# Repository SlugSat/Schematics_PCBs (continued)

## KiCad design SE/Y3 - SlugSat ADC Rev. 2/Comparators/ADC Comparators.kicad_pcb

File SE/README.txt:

Rad Team Six shall live forever in our Memories

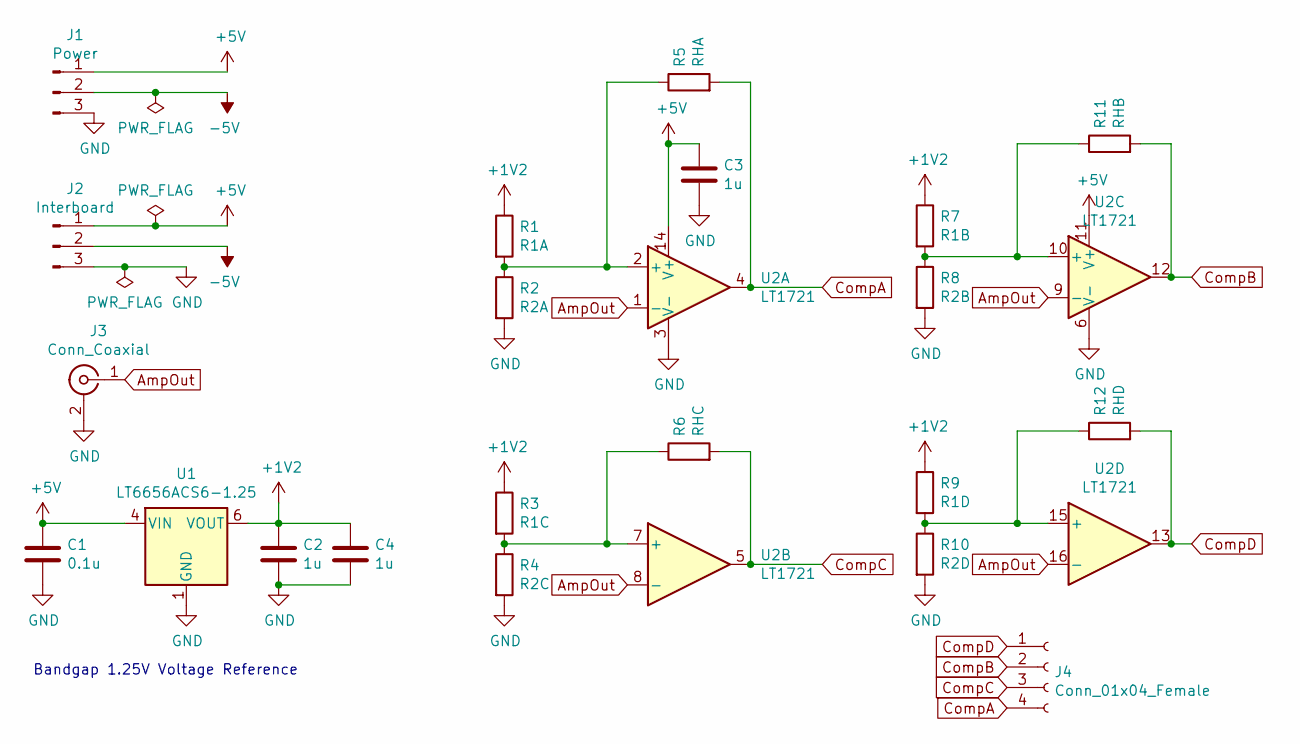
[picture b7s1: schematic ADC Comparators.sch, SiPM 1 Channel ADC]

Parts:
C1: 0.1u; C_0805_2012Metric_Pad1.15x1.40mm_HandSolder
C2, C3, C4: 1u; C_0805_2012Metric_Pad1.15x1.40mm_HandSolder
J1: Power; PinSocket_1x03_P2.54mm_Vertical
J2: Interboard; PinSocket_1x03_P2.54mm_Vertical
J3: Conn_Coaxial; SMA_Amphenol_132289_EdgeMount
J4: Conn_01x04_Female; PinSocket_1x04_P2.54mm_Vertical
R1: R1A; R_0805_2012Metric_Pad1.15x1.40mm_HandSolder
R2: R2A; R_0805_2012Metric_Pad1.15x1.40mm_HandSolder
R3: R1C; R_0805_2012Metric_Pad1.15x1.40mm_HandSolder
R4: R2C; R_0805_2012Metric_Pad1.15x1.40mm_HandSolder
R5: RHA; R_0805_2012Metric_Pad1.15x1.40mm_HandSolder
R6: RHC; R_0805_2012Metric_Pad1.15x1.40mm_HandSolder
R7: R1B; R_0805_2012Metric_Pad1.15x1.40mm_HandSolder
R8: R2B; R_0805_2012Metric_Pad1.15x1.40mm_HandSolder
R9: R1D; R_0805_2012Metric_Pad1.15x1.40mm_HandSolder
R10: R2D; R_0805_2012Metric_Pad1.15x1.40mm_HandSolder
R11: RHB; R_0805_2012Metric_Pad1.15x1.40mm_HandSolder
R12: RHD; R_0805_2012Metric_Pad1.15x1.40mm_HandSolder
U1: LT6656ACS6-1.25; TSOT-23-6_HandSoldering
U2: LT1721; SOIC-16_3.9x9.9mm_P1.27mm

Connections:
+1V2: C2.1, C4.1, R1.1, R3.1, R7.1, R9.1, U1.6 (VOUT)
+5V: C1.1, C3.1, J1.1, J2.1, U1.4 (VIN), U2.11 (V+), U2.14 (V+)
-5V: J1.2, J2.2
AmpOut: J3.1 (In), U2.1 (-), U2.8 (-), U2.9 (-), U2.16 (-)
CompA: J4.4, R5.2, U2.4
CompB: J4.2, R11.2, U2.12
CompC: J4.3, R6.2, U2.5
CompD: J4.1, R12.2, U2.13
GND: C1.2, C2.2, C3.2, C4.2, J1.3, J2.3, J3.2 (Ext), R2.2, R4.2, R8.2, R10.2, U1.1 (GND), U1.2 (GND), U2.3 (V-), U2.6 (V-)
unnamed: R1.2, R2.1, R5.1, U2.2 (+)
unnamed: R3.2, R4.1, R6.1, U2.7 (+)
unnamed: R9.2, R10.1, R12.1, U2.15 (+)
unnamed: R7.2, R8.1, R11.1, U2.10 (+)

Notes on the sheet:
Bandgap 1.25V Voltage Reference

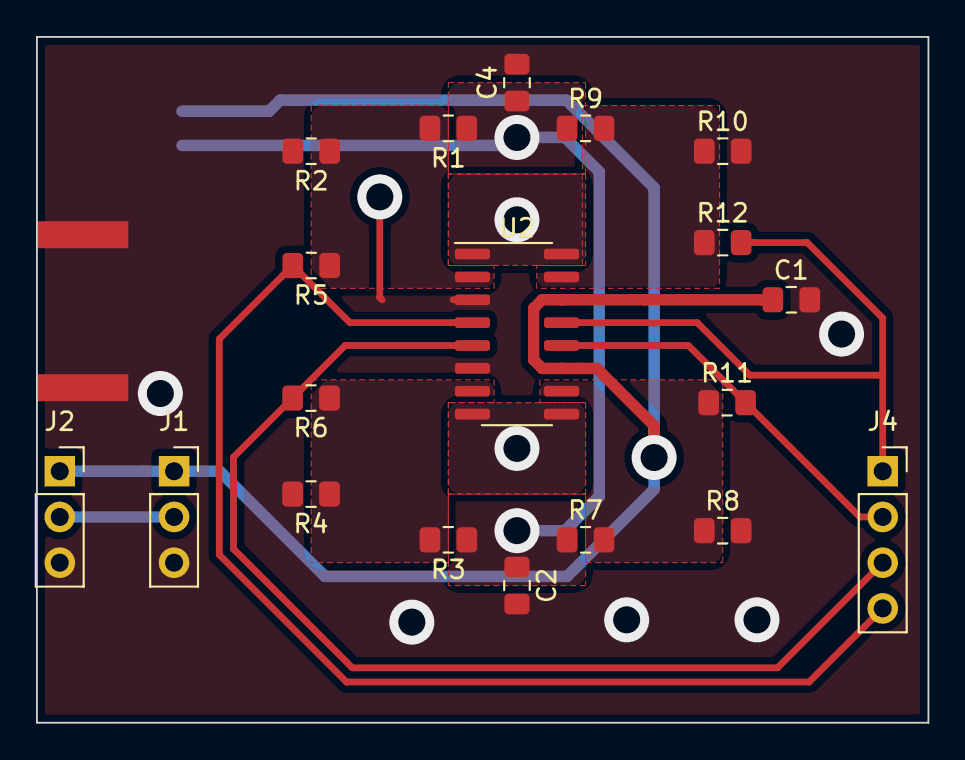
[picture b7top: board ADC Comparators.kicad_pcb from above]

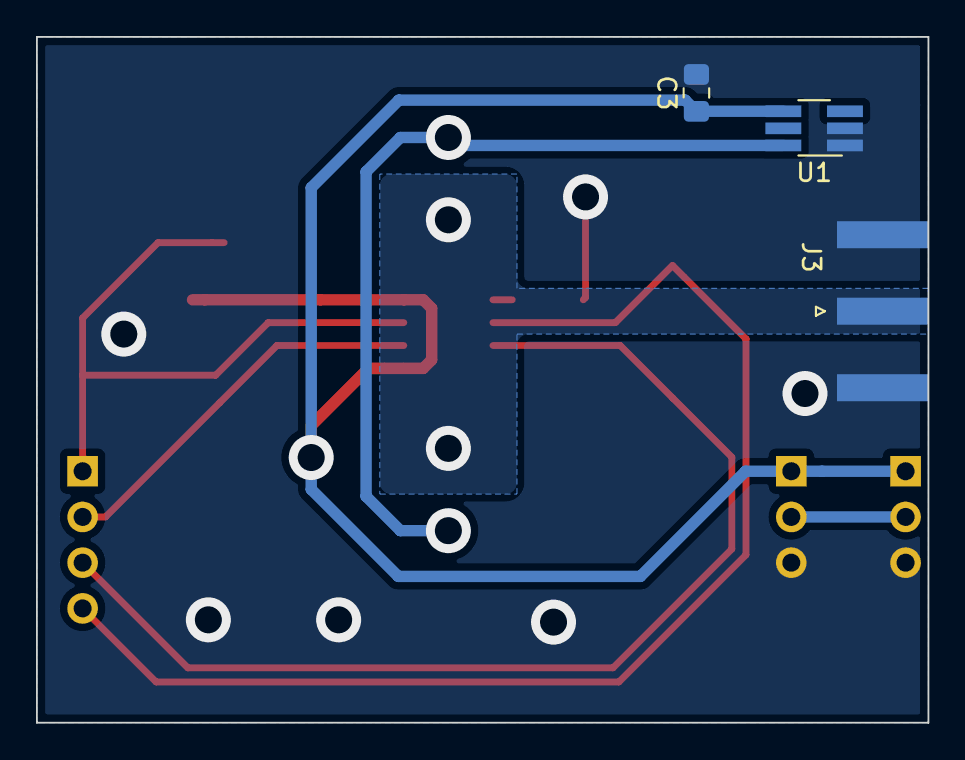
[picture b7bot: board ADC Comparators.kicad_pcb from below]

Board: 2 copper layers, 49.5 x 38.1 mm, 22 parts (3 on the bottom side), 13 nets.

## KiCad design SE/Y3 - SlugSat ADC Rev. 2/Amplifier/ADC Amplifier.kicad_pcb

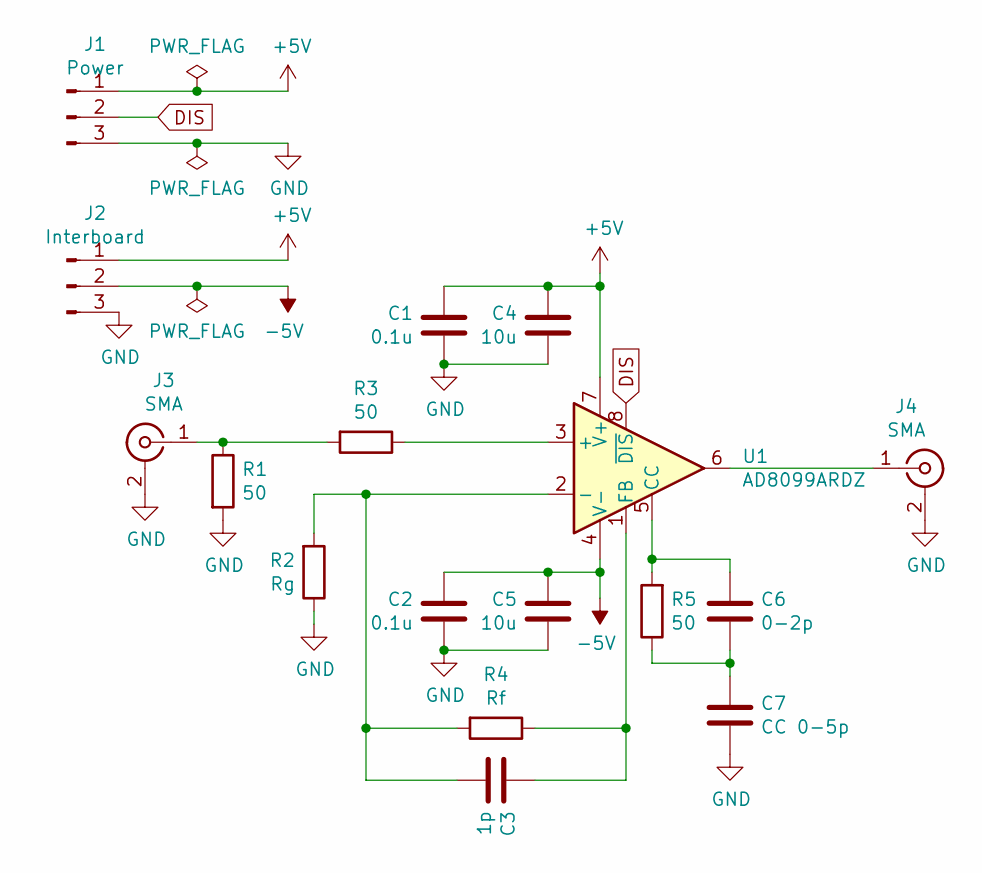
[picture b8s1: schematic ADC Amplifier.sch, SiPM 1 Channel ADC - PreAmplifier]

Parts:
C1, C2: 0.1u; C_0805_2012Metric_Pad1.15x1.40mm_HandSolder
C3: 1p; C_0805_2012Metric_Pad1.15x1.40mm_HandSolder
C4, C5: 10u; C_Elec_4x5.4
C6: 0-2p; C_0805_2012Metric_Pad1.15x1.40mm_HandSolder
C7: CC 0-5p; C_0805_2012Metric_Pad1.15x1.40mm_HandSolder
J1: Power; PinSocket_1x03_P2.54mm_Vertical
J2: Interboard; PinSocket_1x03_P2.54mm_Vertical
J3, J4: SMA; SMA_Amphenol_132289_EdgeMount
R1, R3, R5: 50; R_0805_2012Metric_Pad1.15x1.40mm_HandSolder
R2: Rg; R_0805_2012Metric_Pad1.15x1.40mm_HandSolder
R4: Rf; R_0805_2012Metric_Pad1.15x1.40mm_HandSolder
U1: AD8099ARDZ; SOIC-8_3.9x4.9mm_P1.27mm

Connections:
+5V: C1.1, C4.1, J1.1, J2.1, U1.7 (V+)
-5V: C2.1, C5.1, J2.2, U1.4 (V-)
DIS: J1.2, U1.8 (~DIS)
GND: C1.2, C2.2, C4.2, C5.2, C7.2, J1.3, J2.3, J3.2 (Ext), J4.2 (Ext), R1.2, R2.1, U1.9 (GND)
unnamed: C3.1, R4.1, U1.1 (FB)
unnamed: C3.2, R2.2, R4.2, U1.2 (-)
unnamed: C6.1, R5.2, U1.5 (CC)
unnamed: C6.2, C7.1, R5.1
unnamed: J3.1 (In), R1.1, R3.2
unnamed: J4.1 (In), U1.6
unnamed: R3.1, U1.3 (+)

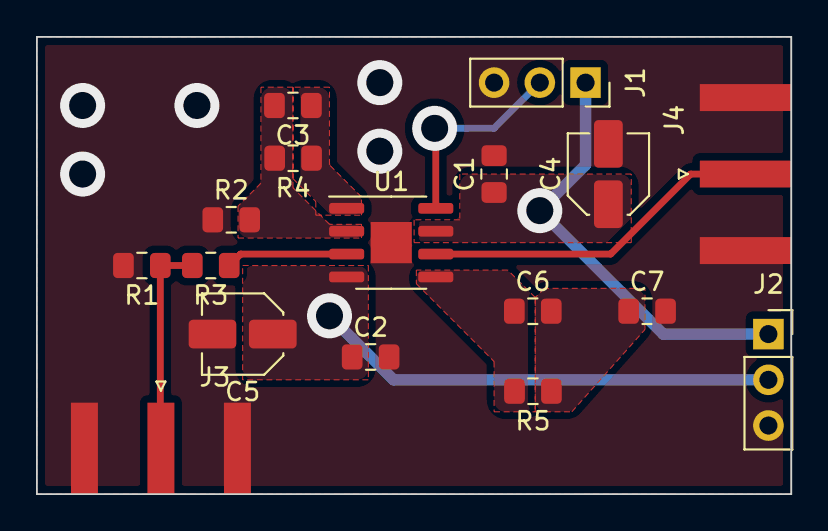
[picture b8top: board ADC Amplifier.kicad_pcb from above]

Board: 2 copper layers, 41.9 x 25.4 mm, 17 parts (0 on the bottom side), 11 nets.

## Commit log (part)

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2020-01-04 created folder for footprints and schematics. created folders for all sub teams. Populated LT schematics and PCB files
2020-01-04 needed ssh key
2020-01-10 Update test-file.txt
    dummy text
2020-01-15 added edge cuts
2020-01-16 added README files for the rest of the subteams
2020-01-16 added read me to all subteam folders
2020-01-16 created 29.4MHz LPF Schematic
2020-01-16 Created Variable Capacitor footprint. Completed rev0 of 29.4MHz low-pass filter.
2020-01-17 removed 0 ohm resistors on 29.4MHz LPF
2020-01-18 removed 0 ohm resistors
2020-01-19 added PLL PSPICE simulations
2020-01-19 29.4 MHz Bandpass Added
    I put all of my documents regarding the 29.4 MHz Bandpass Filter onto Git
2020-01-22 created notch filter schematic
2020-01-22 created schematic symbol and footprint for 7m3 inductor. laid out PCB
2020-01-25 changing EMS file name to EPS
2020-01-29 created README
2020-01-29 PLL and bandstop PSPICE changes
2020-01-29 removed README due to merge conflict?? i just added it back in. no other changes were made. sorry EPS
2020-01-30 creating basic schematic of SPV1040 charger
2020-02-01 changed power amplifier pcb layout again
2020-02-02 added RF transformer datasheets in the PA folder
2020-02-02 adding spreadsheet that includes calculations for SPV1040
2020-02-03 Added SS.lib to schematic libraries, Added SS.pretty to footprints, added .stp to /Chassis
2020-02-04 adding README for calculations folder within SPV1040 and moving paramters of python code to top
2020-02-04 adding resistor values found from 308 inventory spreadsheet
2020-02-04 updating github
2020-02-04 Changes to 29.4 MHz Bandpass Filter
    I made some changes to my best filter design, allowing for series inductors
2020-02-04 added step file to A1 and B1
2020-02-04 fixed step file for A1 and B1
2020-02-05 Kicad Valentine's File
    Just in case you want to edit the text for the heart, but keep the heart itself, I uploaded the kicad PCB file
2020-02-05 made mechanical drawings for STD PCB's
2020-02-06 fixed Step files for A1/A2/B1/B2
2020-02-06 no changes to bandpass filter
2020-02-07 Variable Inductors, 5th Order Chev, Kicad Tutorial
    - I made a Filter with variable inductors
    - I made a 5th order Chebyshev Filter
    - I made a folder to put Kicad tutorial testing files in
2020-02-08 added PA rev 2.0 schematic
2020-02-08 adding datasheet for potential capacitor
2020-02-08 Finished PA Rev 2.0 layout and ready to mill
2020-02-10 Clock Test board v1.0
2020-02-11 Saved schematic and PCB
2020-02-11 add footprint to library
2020-02-12 created down mixer schematic in kicad
2020-02-13 created mixer schematic and rev2 with impedance matching w/o transormers (single-ended)
2020-02-14 Added 50 Ohm microstrip to SS.lib and SS.pretty
2020-02-14 fixed Clock Test
2020-02-15 LNA uploaded to Kicad
    I recreated Year 2's LNA board on Kicad and made a quick PCB
2020-02-15 Bandpass Filter Cleaning
    I reorganized the 29.4 MHz bandpass filter designs so it's more readable in the folders, and shows which file is the final design
2020-02-15 created layout for single-ended down mixer
2020-02-16 swapped edge mount footprint. created gerber and drill files.
2020-02-17 completing the values for capacitors in SPV1040 and choosing the diode for over output voltage...Adding 0 ohm resistor for XSHUT descision later
2020-02-17 PA rev 3.0 schematic and footprint association complete
2020-02-18 updated footprint assignments to daughter board
2020-02-18 revised PA rev 3.0 schematic and started PCB layout
2020-02-18 Fixed PA rev 2.0 schematic values for PA rev 2.1
2020-02-18 Finished Mother Board
    Each of the Components have been placed to the mother board
2020-02-18 Daughter Board
    Began annotating the rest of the Daughter board
2020-02-19 Finished Daughter Board
    I finished assigning the footprints to the daughter board
2020-02-19 Just a push check
    idk if I pushed
2020-02-19 Messing With Resistors
    Just doing some resistor changes but idk if it worked
2020-02-19 LMX2313 3D view
    Added an imposted 3D viewer for the LMX2313
2020-02-19 Added LMX2313 3D again
2020-02-19 finished Mobo footprint/3D placement
2020-02-19 making multiple changes to board. Changing capacitor at input and output to 100uF and adding footprints to pcb
2020-02-19 adding TSSOP8 footprint into SS footprint library for SPV1040. Also referenced footprint to the one in SS within the PCB layout
2020-02-19 finshed assigning step files for integration boards
2020-02-19 removed step files from repo because they were large files
2020-02-19 changing input values into float to take decimals
2020-02-19 creating schematic for Lithion charger l6924 and adding schematic symbol into library ss
2020-02-20 Finished Variable Gain Amplifier
    I finished moving the Variable Gain Amplifier onto Kicad, following the board layout made by Sage
2020-02-21 remaking schematic from Pierce back to Colpitts
2020-02-21 MoBo Pretty
    Made some changes to the MoBo which included changing the outline boarders for the sheets
2020-02-21 working on voting circuit
2020-02-22 completing charging circuit L6924D
2020-02-23 adding the SS schematic and footprint library
2020-02-23 adding L6924D footprint into SS footprint library
2020-02-23 shrinking pcb layout
2020-02-23 PLL Stability Test Rev0 Schematic
    I made a new folder for the PLL stability test. I began placing generic 8 pin op-amps between the loop filter and the VCO
2020-02-23 Cleaned Up Stability Test Board
    Made the schematic page bigger
2020-02-23 Bwtest rev2
    Uploaded burn wire rev2 .drl files
2020-02-23 -5V
    Added -5V rail
2020-02-23 -5V rail updates
    -5V rail schematic
2020-02-23 saving
2020-02-25 Pre-Amp File
    I fully integrated the Pre-amp onto KiCad
2020-02-25 Stability Test PCB design
    I laid out the PCB for the stability test
2020-02-25 Added label for Stability Board
2020-02-26 adding ignore file
2020-02-26 gitignore for kicad files
2020-02-27 completed down-mixer rev0.1 schematic and layout. generated milling files
2020-02-27 Added 40.1 MHz LPF on KiCad
    I added the 40.1 MHz Low Pass Filter onto KiCad
2020-02-28 New footprint
    Added SL03 Vishay footprint
2020-02-28 added footprint into SS.pretty for EPS
2020-02-29 Imported Rev4.01, 4.02, 4.03 to Kicad
    Put Rev4.01, Rev4.02, and Rev4.03 onto KiCad
2020-02-29 Revised PA Rev 3.0 layout to fix transformers from coupling
2020-02-29 Finished PLL Revisions on KiCad
    The KiCad files for the PLL have been uploaded to github and the integration to the "Real Resistor" symbol has begun
2020-03-01 Nothing Really
2020-03-01 Changed Resistor Symbols
    Fixed the resistor symbols from PLL Rev 4.1-4.3
2020-03-02 Just Testing GitBash, changed a resistor value in LNA
2020-03-02 removed .net from .gitignore
2020-03-02 Added a symbol to one of the notch filters
2020-03-02 add dummy component
2020-03-02 Important changes to notch filter
2020-03-03 -5V rail
    -5V rail updated layout
2020-03-04 files
    files
2020-03-04 Made a separate op-amp board
2020-03-05 completed PLL stability test layour for individual boards
2020-03-05 Nothing much I don't think
2020-03-06 Finished the layout for the Op-Amp Test Board with Capacitors
2020-03-06 .DS_store files
    File changes
2020-03-06 -5V Rail
    Updated PCB layout
2020-03-06 -5V Rail
    Update 2 PCB layout
2020-03-06 added PA coupler datasheet
2020-03-07 changing scalar and bias due to improvement in dummy circuit
2020-03-07 manipulated bais to get better values
2020-03-07 PA Rev 4.0 layout is complete. PCB is ready to be milled
2020-03-08 Added the schematic for SE's flash memory board
2020-03-09 Added PA Rev 4.1 KiCAD schematic files
2020-03-09 PA Rev 4.1 KiCAD schematic complete.
2020-03-09 PA Rev 4.1 KiCAD schematic and footprint association is complete. Ready for PCB layout
2020-03-09 PA Rev 4.1 PCB layout still in progress.
2020-03-10 Finished SE Flash Memory Schematic
2020-03-10 finishing 1.5 version of spv1040
2020-03-10 3.3V Rail
    Schematic
2020-03-10 Changed an input pin to the flash memory for SE schematic
2020-03-11 created matlab files for VCO. updated phase detector board for stability test
2020-03-11 Update 3.3V_Rail.sch
    Update v.0.1
2020-03-12 added second matlab vco sim
2020-03-12 -5V rail
    Schematic update
2020-03-17 03/16/2020 10:07 PM. last commit from UCSC campus. good bye.
2020-04-01 Trying stuff
2020-04-06 I uploaded the schematics for the receiving stage into their respective hierarchial sheets and have begun the integration of the received stage
2020-04-08 Added simple amplifier simulation to get used to simulink
2020-04-08 simple amplifier model (SAM) simulink simulation works!
2020-04-10 Included a graph of for my self made VCO which shows the frequency change with a change in 0-5V, with steps of 0.2V
2020-04-11 Uploaded a version of the Self Made VCO which removes the unwanted complex portion of the phase noise. Also added in a Rev0 of a PLL which locks at 20 MHz.
2020-04-11 added wire to detector on Dobo
2020-04-11 Added a comment to the VGA...I think...
2020-04-18 Added the file for the MoBo EU integration, the second stage for the individual stage integration steps
2020-04-20 Finished PA schematic on MOBO integration
2020-04-21 Transmitting stage annotations are done. Ready to layout PCB for rev0
2020-04-22 Finished 29.4 MHz BPF PCB Layout. 1/4 boards complete for transmitting stage integration
2020-04-22 Uploaded Schematics to Integration of Phase 2
2020-04-22 Finished pre-amplifier PCB layout. 2/4 circuits complete for transmitting stage integration for LT
2020-04-22 Integration of LT transmitting stage dev0 board is complete
2020-04-22 I guess I added a low pass filter file? I don't think it's anything though
2020-04-23 Added the preliminary layout for the Phase 2 motherboard, not at all finished yet
2020-04-27 EPS rails updated
2020-05-04 Fixed phase 3 integration folder for Mobo
2020-05-05 adding the file for phase 3 of the daughterboard
2020-05-06 Finished the preliminary layout of the receiving stage for MoBo Phase 3
2020-05-09 Finished schematic layout of Pre Amplifier
2020-05-09 Finished 29.4 MHz LPF layout. PCB Layout of Transmitting Stage for Phase 3 is ready to be laid out
2020-05-09 Finished 29.4 MHz LPF PCB layout for Phase 3 of Transmitting Stage. 2/4 Complete
2020-05-09 Fixed some minor layout issues on the motherboard
2020-05-11 SiPM footprint
2020-05-11 Changed 2pin headers to 5pin headers for output of pre-amp and input of PA
2020-05-11 Annotated Phase 3 Motherboard Block Diagram
2020-05-13 created A2D schematic
2020-05-14 rearranged file order levels
2020-05-14 incorporated A2D with SiPM, main work continueing from here is the Detector schematic and maybe the A2D references. in the Detector the SiPM needs to be changed to the Broadcom SiPM and the CSP needs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
2020-05-14 Reviewed 32V rail
2020-05-14 Progressed PS
2020-05-15 top level schematic pre-design review. after feedback from Petersen there is much to change specifically in the A2D section
2020-05-18 Making sure my KiCad files were pushed
2020-05-21 finished up A2D stuff and OR stuff whats left is updating the bus to reflect the old v0.4 from Winter and then ORing the outputs at the high level for the ISR and reconnecting the ISR, DATA, selector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
2020-05-21 Radiation Detector SHOULD be PDR ready :3
2020-05-21 typo in Det4
2020-05-23 Fixed the hierarchy for the MoBo Phase 3
2020-05-23 SiPM schematic symbol modified
2020-05-24 cleaned up schematic and clarified
2020-05-25 35V rail updates
2020-06-03 Accessed Year 3 flat sat
2020-06-03 Added folder for updated 3.3V rail
2020-06-03 Added -5V rail updated design
2020-06-06 changed file name
2020-06-06 forgot to update .pdf
2020-06-07 added SE.pdf
2020-07-13 uploaded the final schematics for the integration
2022-01-18 test 2
2022-01-20 I am trying to push my duplexer schematic
2022-01-20 test push a readme
2022-01-20 I worked more on the duplexer by adding the sma connectors
2022-01-22 Pushing initial ADS files for Rev 4.1
2022-05-17 Preamplifier KiCad Revisions
2022-05-19 I created the Duplexer Revision 0.3 KiCad File and added my design into it
2022-05-20 I added more variable caps and inductors to the Duplexer Rev0.3 KiCad design
2022-05-25 I begin working on my duplexer rev0.31 in KiCad, I also added the needed footprints and symbols to the github
2022-06-01 I completed my final schematic with new footprints for the Duplexer Rev0.31
